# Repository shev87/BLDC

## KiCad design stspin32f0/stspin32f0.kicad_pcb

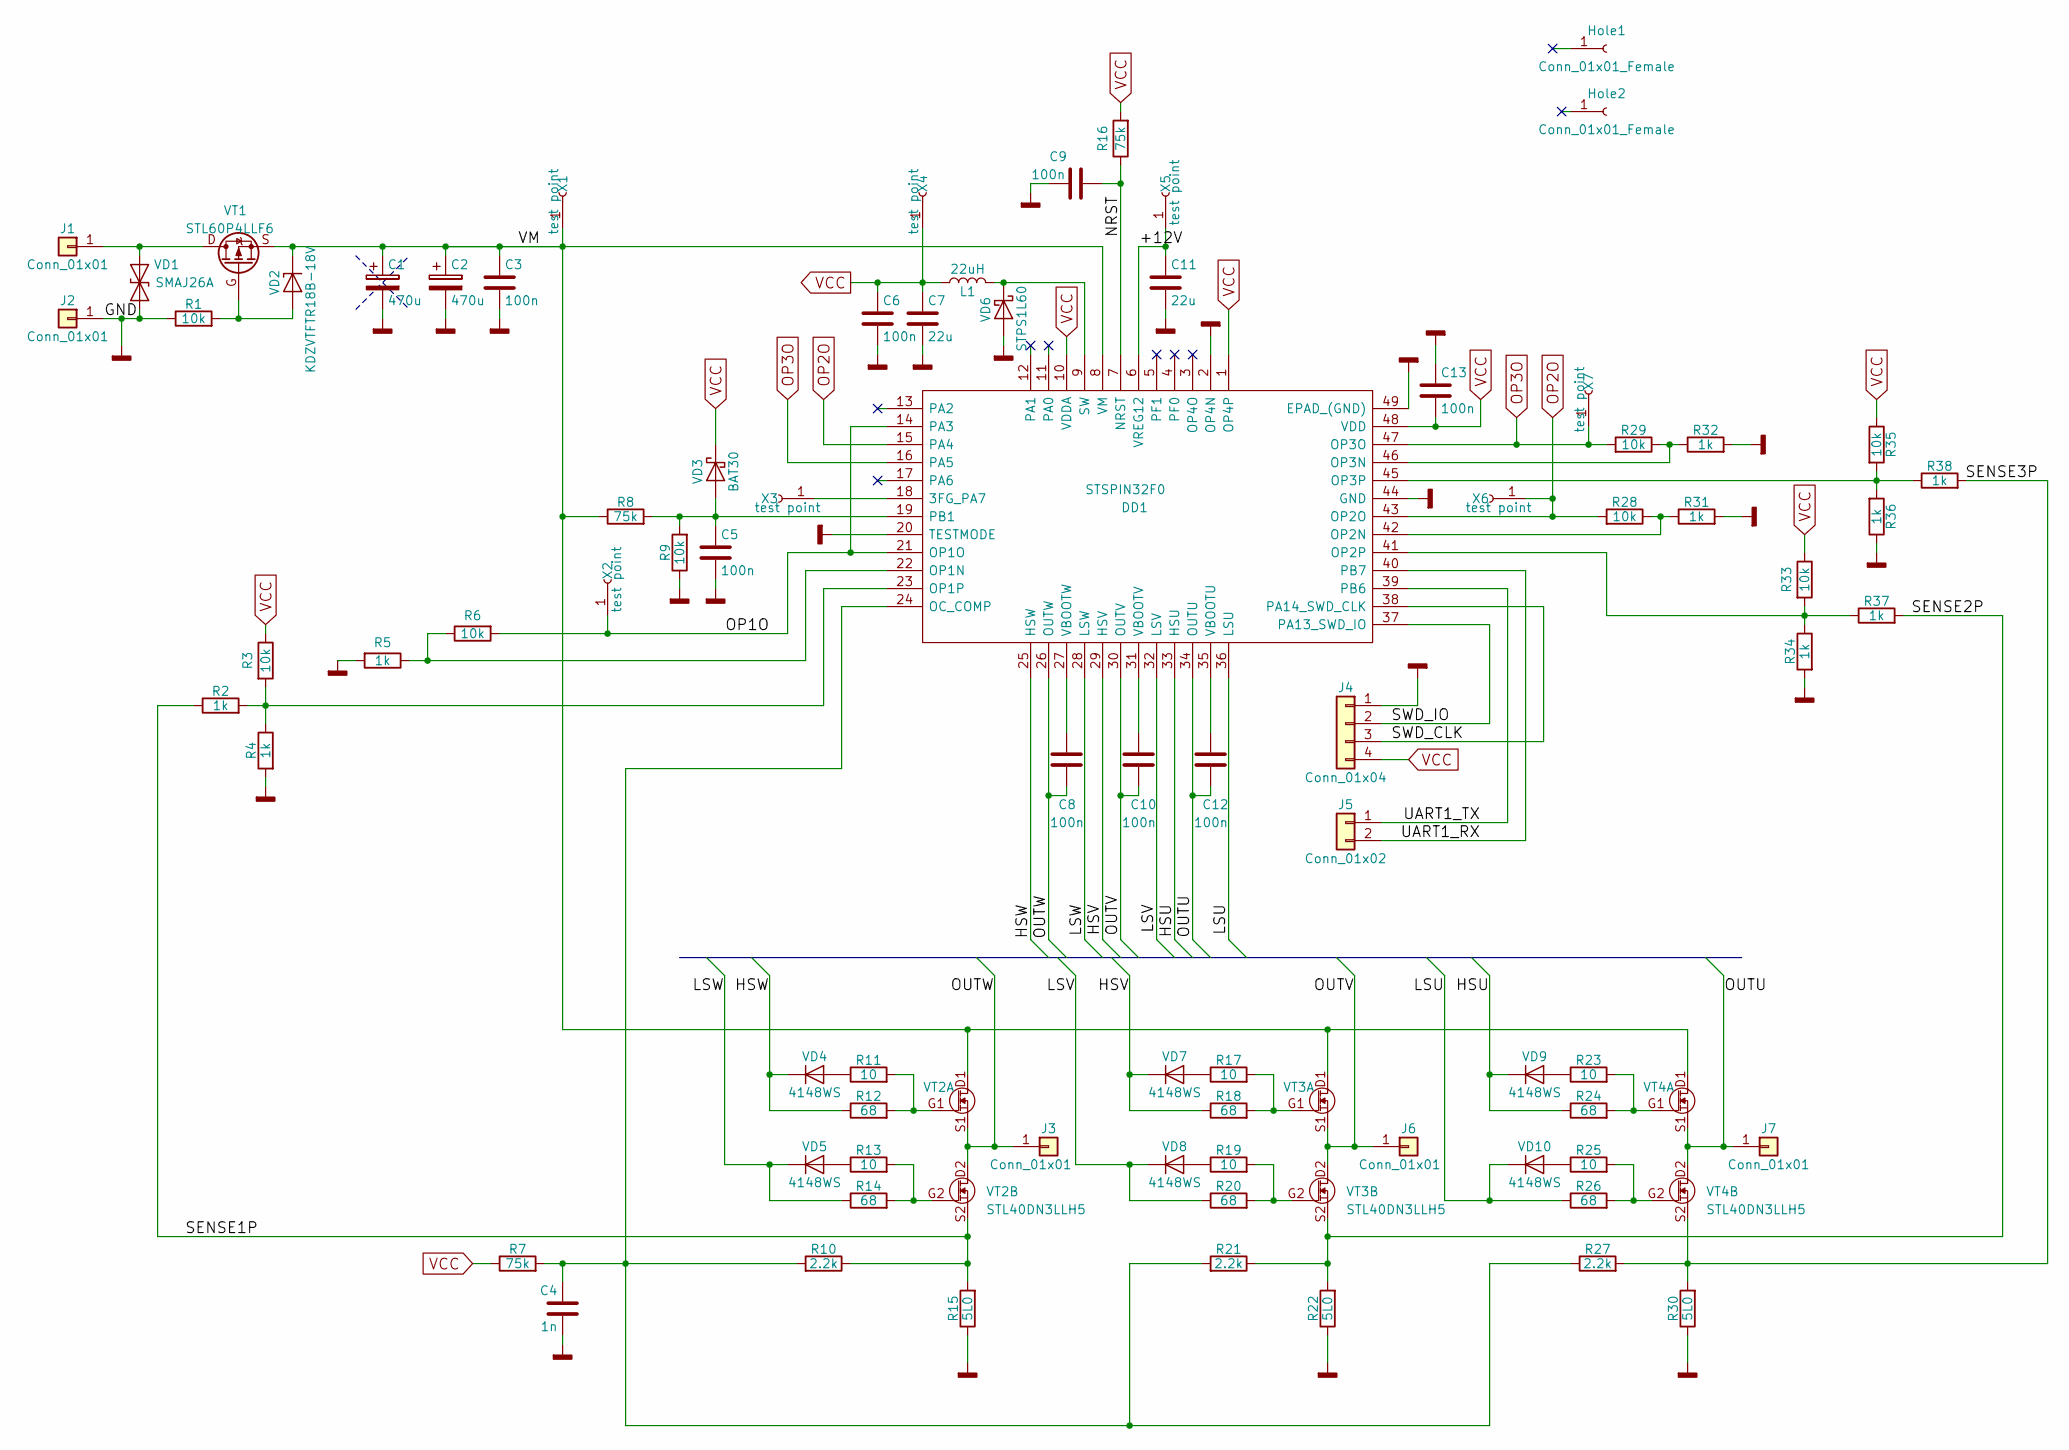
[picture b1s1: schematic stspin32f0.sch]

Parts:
C1: 470u; CP_Elec_10x10.5
C2: 470u; CP_Radial_D10.0mm_P5.00mm
C3, C5, C6, C8, C9, C10, C12, C13: 100n; C_0603
C4: 1n; C_0603
C7, C11: 22u; C_1206
DD1: STSPIN32F0; QFN50P700X700X100-49N-D; Mouser Part Number 511-STSPIN32F0
Hole1, Hole2: Conn_01x01_Female; hole3.2w6.2
J1, J2: Conn_01x01; SolderWirePad_single_2.7mmDrill0.8Via6.2Width
J3, J6, J7: Conn_01x01; SolderWirePad_single_1.5mmDrill0.5Via4.0Width
J4: Conn_01x04; Socket_Strip_Straight_1x04_Pitch2.54mm_SMD
J5: Conn_01x02; Socket_Strip_Straight_2x01_Pitch1.27mm_SMD
L1: 22uH; L_1206
R1, R3, R6, R9, R28, R29, R33, R35: 10k; R_0603
R2, R4, R5, R31, R32, R34, R36, R37, R38: 1k; R_0603
R7, R8, R16: 75k; R_0603
R10, R21, R27: 2.2k; R_0603
R11, R13, R17, R19, R23, R25: 10; R_0603
R12, R14, R18, R20, R24, R26: 68; R_0603
R15, R22, R30: 5L0; R_2512
VD1: SMAJ26A; D_SMA
VD2: KDZVTFTR18B-18V; D_SOD-123F; Manufacturer Part Number BZV55-B3V3
VD3: BAT30; D_SOD-523; Manufacturer Part Number BAT30KFILM
VD4, VD5, VD7, VD8, VD9, VD10: 4148WS; D_SOD-323
VD6: STPS1L60; D_SMA; Manufacturer Part Number STPS1L60A
VT1: STL60P4LLF6; PowerFLAT-5x6-Single
VT2: STL40DN3LLH5; PowerFLAT-5x6_withVias; Manufacturer Part Number STL40DN3LLH5; Mouser Part Number 511-STL64DN4F7AG
VT3, VT4: STL40DN3LLH5; PowerFLAT-5x6_withVias; Manufacturer Part Number STL64DN4F7AG; Mouser Part Number 511-STL64DN4F7AG
X1, X2, X3, X4, X5, X6, X7: test point; testPoint

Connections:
/+12V: C11.1, DD1.6 (VREG12), X5.1
/HSU: DD1.33 (HSU), R24.1, VD9.1 (K)
/HSV: DD1.29 (HSV), R18.1, VD7.1 (K)
/HSW: DD1.25 (HSW), R12.1, VD4.1 (K)
/LSU: DD1.36 (LSU), R26.1, VD10.1 (K)
/LSV: DD1.32 (LSV), R20.1, VD8.1 (K)
/LSW: DD1.28 (LSW), R14.1, VD5.1 (K)
/NRST: C9.1, DD1.7 (NRST), R16.1
/OP1O: DD1.14 (PA3), DD1.21 (OP1O), R6.2, X2.1
/OUTU: C12.2, DD1.34 (OUTU), J7.1, VT4.D2 (D), VT4.S1 (S)
/OUTV: C10.2, DD1.30 (OUTV), J6.1, VT3.D2 (D), VT3.S1 (S)
/OUTW: C8.2, DD1.26 (OUTW), J3.1, VT2.D2 (D), VT2.S1 (S)
/SENSE1P: R2.1, R10.1, R15.2, VT2.S2 (S)
/SENSE2P: R21.1, R22.2, R37.2, VT3.S2 (S)
/SENSE3P: R27.2, R30.2, R38.2, VT4.S2 (S)
/SWD_CLK: DD1.38 (PA14_SWD_CLK), J4.3
/SWD_IO: DD1.37 (PA13_SWD_IO), J4.2
/UART1_RX: DD1.40 (PB7), J5.2
/UART1_TX: DD1.39 (PB6), J5.1
/VM: C1.1, C2.1, C3.1, DD1.8 (VM), R8.1, VD2.1 (K), VT1.S, VT2.D1 (D), VT3.D1 (D), VT4.D1 (D), X1.1
GNDD: C1.2, C2.2, C3.2, C4.2, C5.2, C6.2, C7.2, C9.2, C11.2, C13.1, DD1.2 (OP4N), DD1.20 (TESTMODE), DD1.44 (GND), DD1.49 (EPAD_(GND)), J2.1, J4.1, R1.1, R4.2, R5.2, R9.1, R15.1, R22.1, R30.1, R31.2, R32.2, R34.2, R36.1, VD1.2 (A2), VD6.2 (A)
unnamed: C4.1, DD1.24 (OC_COMP), R7.2, R10.2, R21.2, R27.1
unnamed: C5.1, DD1.19 (PB1), R8.2, R9.2, VD3.2 (A)
unnamed: C8.1, DD1.27 (VBOOTW)
unnamed: C10.1, DD1.31 (VBOOTV)
unnamed: C12.1, DD1.35 (VBOOTU)
unnamed: DD1.9 (SW), L1.2, VD6.1 (K)
unnamed: DD1.18 (3FG_PA7), X3.1
unnamed: DD1.22 (OP1N), R5.1, R6.1
unnamed: DD1.23 (OP1P), R2.2, R3.2, R4.1
unnamed: DD1.41 (OP2P), R33.2, R34.1, R37.1
unnamed: DD1.42 (OP2N), R28.1, R31.1
unnamed: DD1.45 (OP3P), R35.2, R36.2, R38.1
unnamed: DD1.46 (OP3N), R29.1, R32.1
unnamed: J1.1, VD1.1 (A1), VT1.D
unnamed: R1.2, VD2.2 (A), VT1.G
unnamed: R11.1, VD4.2 (A)
unnamed: R11.2, R12.2, VT2.G1 (G)
unnamed: R13.1, VD5.2 (A)
unnamed: R13.2, R14.2, VT2.G2 (G)
unnamed: R17.1, VD7.2 (A)
unnamed: R17.2, R18.2, VT3.G1 (G)
unnamed: R19.1, VD8.2 (A)
unnamed: R19.2, R20.2, VT3.G2 (G)
unnamed: R23.1, VD9.2 (A)
unnamed: R23.2, R24.2, VT4.G1 (G)
unnamed: R25.1, VD10.2 (A)
unnamed: R25.2, R26.2, VT4.G2 (G)
OP2O: DD1.15 (PA4), DD1.43 (OP2O), R28.2, X6.1
OP3O: DD1.16 (PA5), DD1.47 (OP3O), R29.2, X7.1
VCC: C6.1, C7.1, C13.2, DD1.1 (OP4P), DD1.10 (VDDA), DD1.48 (VDD), J4.4, L1.1, R3.1, R7.1, R16.2, R33.1, R35.1, VD3.1 (K), X4.1

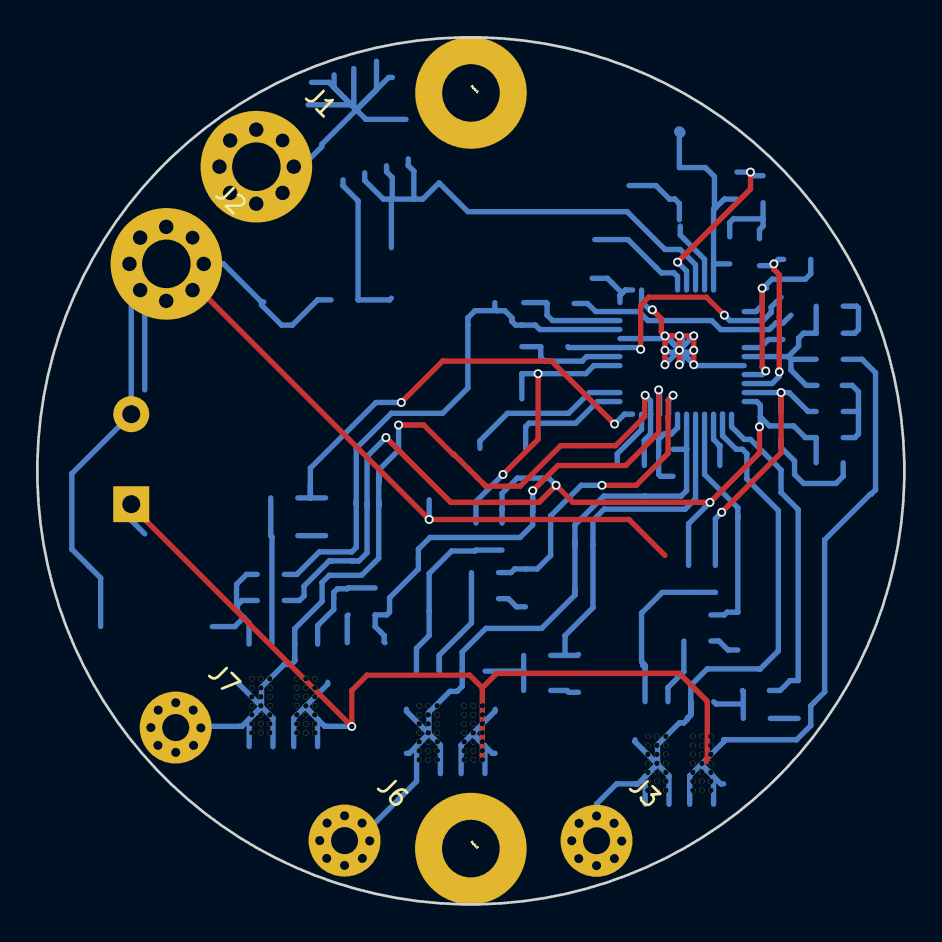
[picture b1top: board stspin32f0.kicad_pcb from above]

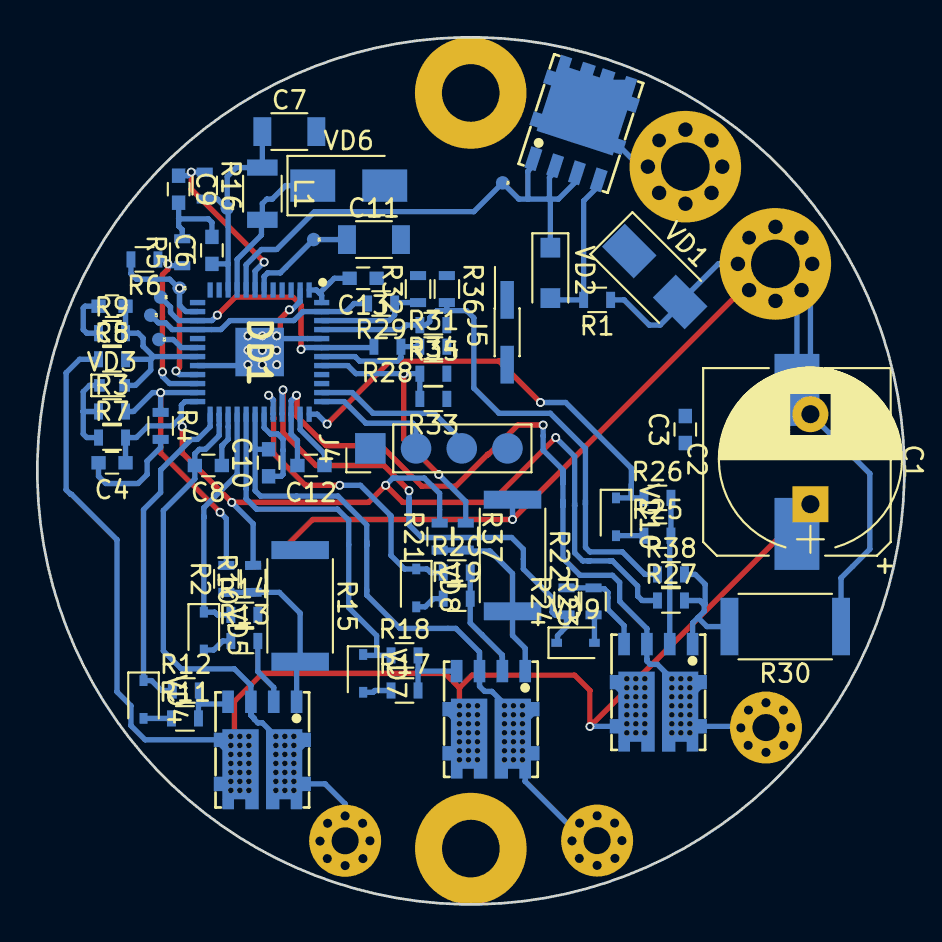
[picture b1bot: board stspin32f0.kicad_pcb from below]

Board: 2 copper layers, 48.2 x 48.2 mm, 83 parts (76 on the bottom side), 51 nets.

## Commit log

2020-04-13 second commit
